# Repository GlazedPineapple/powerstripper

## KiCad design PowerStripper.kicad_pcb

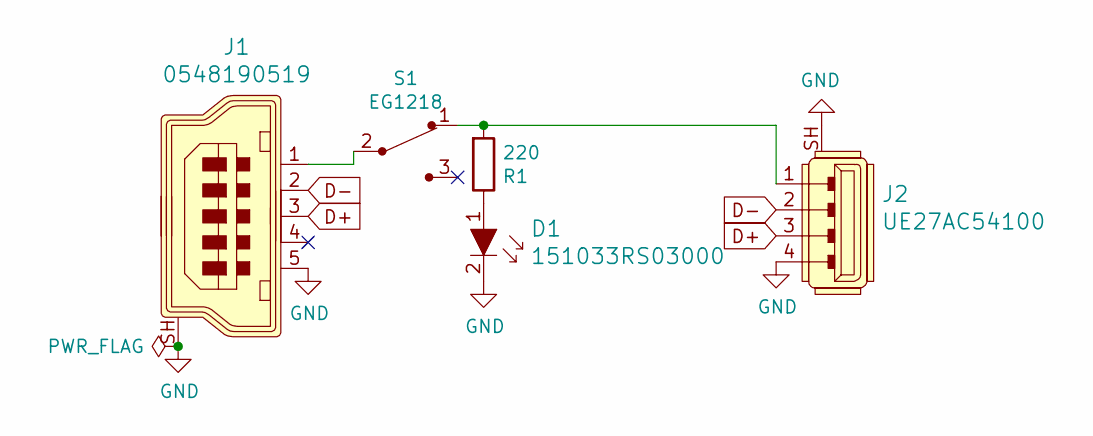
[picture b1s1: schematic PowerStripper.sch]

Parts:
D1: 151033RS03000; LED_3mm_Radial; MPN 151033RS03000; Digi-Key_PN 732-5013-ND
J1: 0548190519; USB_Mini_B_Female_548190519; MPN 0548190519; Digi-Key_PN WM17115-ND
J2: UE27AC54100; USB_A_Female_UE27AC54100; MPN UE27AC54100; Digi-Key_PN UE27AC54100-ND
R1: 220; R_Axial_DIN0207_L6.3mm_D2.5mm_P7.62mm_Horizontal
S1: EG1218; Switch_Slide_11.6x4mm_EG1218; MPN EG1218; Digi-Key_PN EG1903-ND

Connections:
D+: J1.3, J2.3
D-: J1.2, J2.2
GND: D1.2, J1.5, J1.SH, J2.4, J2.SH
unnamed: D1.1, R1.1
unnamed: J1.1, S1.2
unnamed: J2.1, R1.2, S1.1

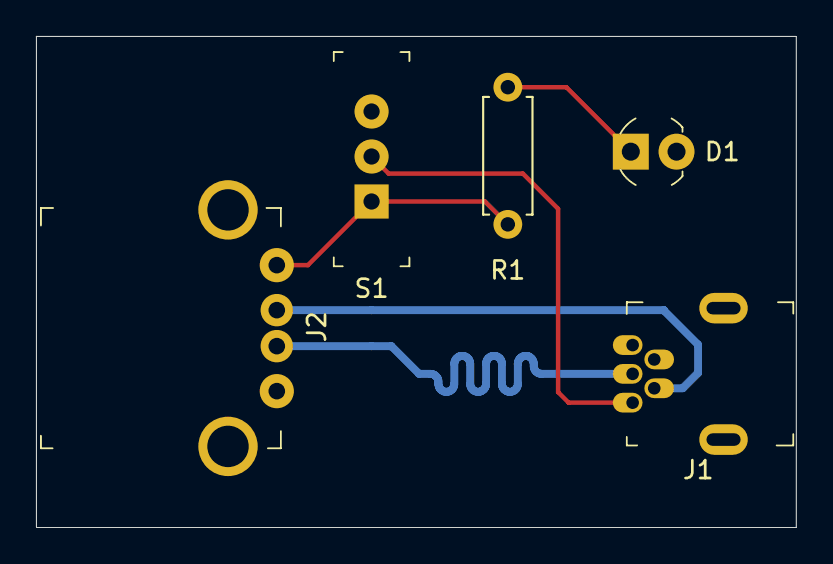
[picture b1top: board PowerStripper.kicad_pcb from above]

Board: 4 copper layers, 42.2 x 27.3 mm, 5 parts (0 on the bottom side), 6 nets.

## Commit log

2021-04-10 Finished the design
2021-04-13 Worked on reorganizing in pcbnew
2021-04-23 made changes to pcb
2021-04-23 added export.zip
2021-04-23 removed old folder
2021-04-23 changed board size
2021-04-23 made more changes to pcb
2021-04-24 So close, yet so far
2021-04-24 Made more changes to board and got closer but it still doesnt work
2021-04-24 closer...
2021-04-24 made some more changes but I think I need to switch to a 4layer board
2021-04-24 Converted to a 4 layer pcb
2021-04-24 fixed issue
2021-04-24 trying to get it to export as 4 layers
2021-04-24 finished
2021-04-24 finished making changes to make it compatible with jlcpcb
2021-04-24 fixed issue in L2
2021-04-24 fixed issue in layers 1 and 4
2021-04-24 ran drc
2021-04-24 updated zip
2021-04-25 fixed export issues
2021-04-25 changed the name of export.zip to powerstripper.zip
2021-04-26 added bottom mask
